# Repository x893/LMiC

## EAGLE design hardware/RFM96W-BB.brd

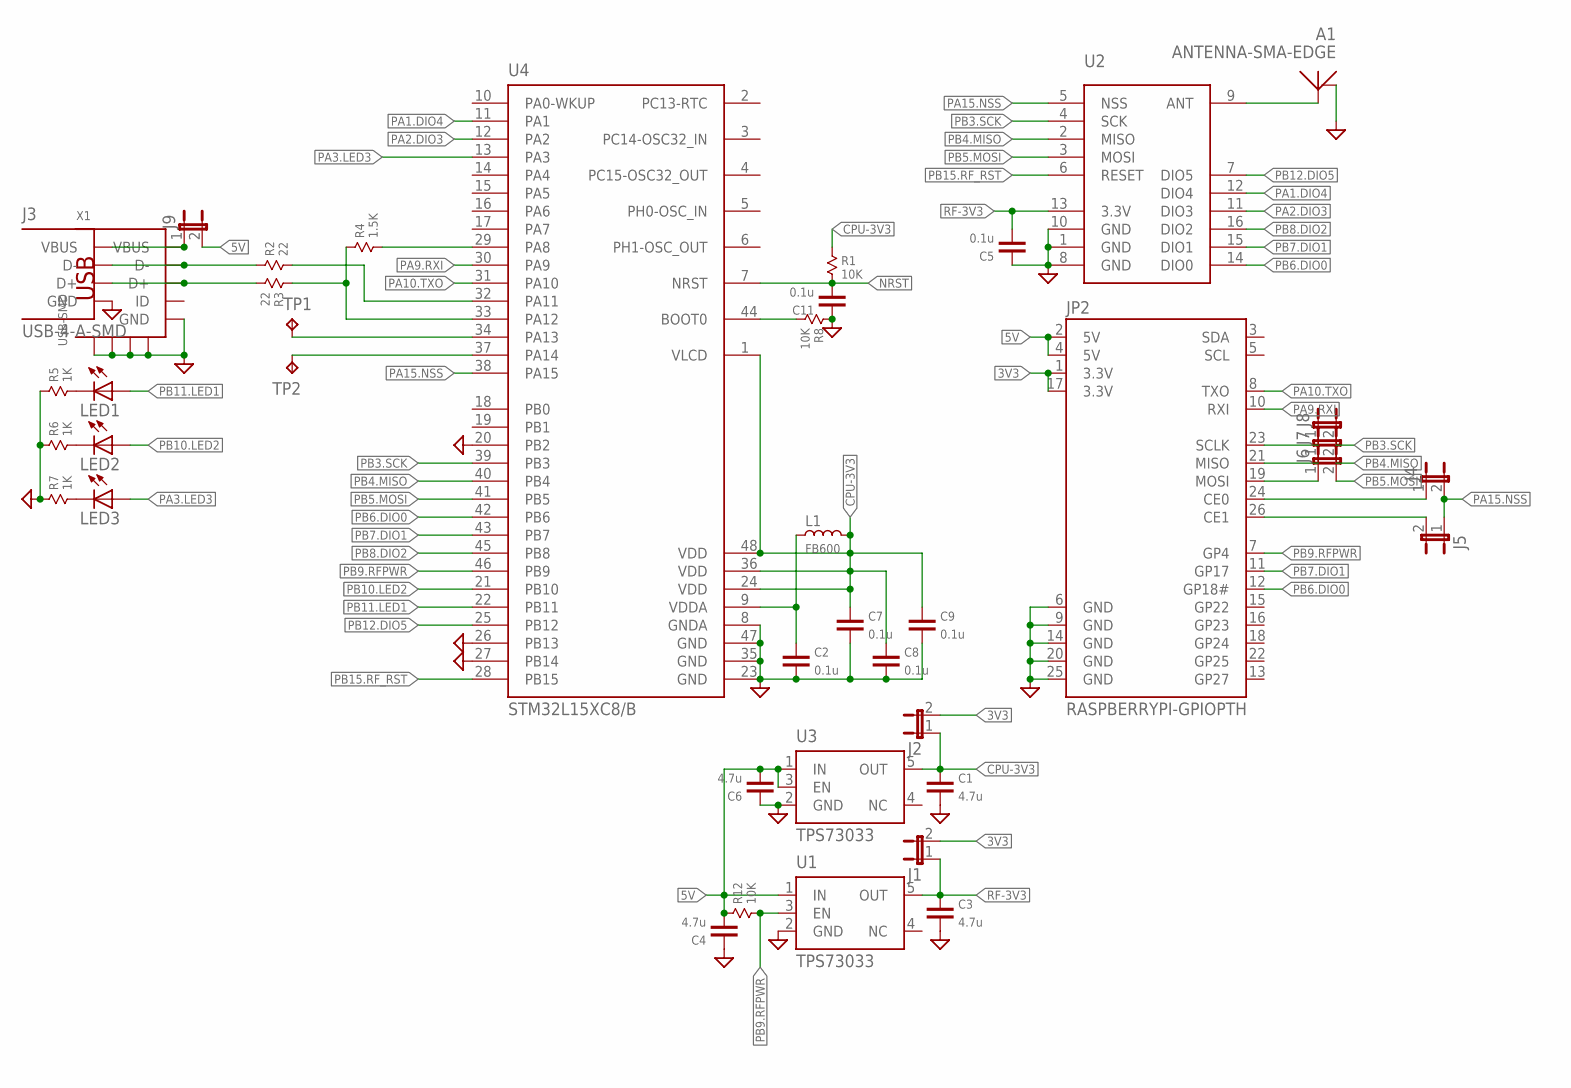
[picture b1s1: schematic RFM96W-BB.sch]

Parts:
A1: ANTENNA-SMA-EDGE; SMA-EDGE
C1, C3, C4, C6: 4.7u; 0603
C2, C5, C7, C8, C9, C11: 0.1u; 0603
J1, J2, J4, J5, J6, J7, J8, J9: JUMPER-2SMD-NO; SJ_2S-NO
J3: USB-4-A-SMD; USB-A-SMD
JP2: RASPBERRYPI-GPIOPTH; 2X13-SHROUDED
L1: FB600; 0603
LED1, LED2, LED3: LEDCHIPLED_0603; CHIPLED_0603
R1, R8, R12: 10K; 0603
R2, R3: 22; 0603
R4: 1.5K; 0603
R5, R6, R7: 1K; 0603
TP1, TP2: TPTP14R; TP14R
U1, U3: TPS73033; SOT23-5
U2: RFM9XW
U4: STM32L15XC8/B; LQFP48
X1: USB-SMD; USB-MINIB

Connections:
3V3: J1.2, J2.2, JP2.1 (3.3V), JP2.17 (3.3V)
5V: C4.1, C6.1, J9.2, JP2.2 (5V), JP2.4 (5V), R12.1, U1.1 (IN), U3.1 (IN), U3.3 (EN)
CPU-3V3: C1.2, C7.2, C8.2, C9.2, J2.1, L1.2, R1.1, U3.5 (OUT), U4.1 (VLCD), U4.24 (VDD), U4.36 (VDD), U4.48 (VDD)
GND: A1.GND@1 (GND), C1.1, C2.1, C3.1, C4.2, C5.2, C6.2, C7.1, C8.1, C9.1, C11.2, J3.GND, JP2.6 (GND), JP2.9 (GND), JP2.14 (GND), JP2.20 (GND), JP2.25 (GND), R5.1, R6.1, R7.1, R8.1, U1.2 (GND), U2.1 (GND), U2.8 (GND), U2.10 (GND), U3.2 (GND), U4.8 (GNDA), U4.20 (PB2), U4.23 (GND), U4.26 (PB13), U4.27 (PB14), U4.35 (GND), U4.47 (GND), X1.GND, X1.GND@1 (GND), X1.GND@2 (GND), X1.GND@3 (GND), X1.GND@4 (GND)
unnamed: C2.2, L1.1, U4.9 (VDDA)
unnamed: A1.ANT, U2.9 (ANT)
unnamed: J3.VUSB (VBUS), J9.1, X1.VBUS
unnamed: J3.D-, R2.1, X1.D-
unnamed: J3.D+, R3.2, X1.D+
unnamed: J8.1, JP2.23 (SCLK)
unnamed: J7.1, JP2.21 (MISO)
unnamed: J4.1, JP2.24 (CE0)
unnamed: J5.2, JP2.26 (CE1)
unnamed: R8.2, U4.44 (BOOT0)
unnamed: LED1.C, R5.2
unnamed: LED2.C, R6.2
unnamed: LED3.C, R7.2
NRST: C11.1, R1.2, U4.7 (NRST)
PA1.DIO4: U2.12 (DIO4), U4.11 (PA1)
PA2.DIO3: U2.11 (DIO3), U4.12 (PA2)
PA3.LED3: LED3.A, U4.13 (PA3)
PA8.D+H: R4.2, U4.29 (PA8)
PA9.RXI: JP2.10 (RXI), U4.30 (PA9)
PA10.TXO: JP2.8 (TXO), U4.31 (PA10)
PA11.D-: R2.2, U4.32 (PA11)
PA12.D+: R3.1, R4.1, U4.33 (PA12)
PA13: TP1.TP, U4.34 (PA13)
PA14: TP2.TP, U4.37 (PA14)
PA15.NSS: J4.2, J5.1, U2.5 (NSS), U4.38 (PA15)
PB3.SCK: J8.2, U2.4 (SCK), U4.39 (PB3)
PB4.MISO: J7.2, U2.2 (MISO), U4.40 (PB4)
PB5.MOSI: J6.2, U2.3 (MOSI), U4.41 (PB5)
PB6.DIO0: JP2.12 (GP18#), U2.14 (DIO0), U4.42 (PB6)
PB7.DIO1: JP2.11 (GP17), U2.15 (DIO1), U4.43 (PB7)
PB8.DIO2: U2.16 (DIO2), U4.45 (PB8)
PB9.RFPWR: JP2.7 (GP4), R12.2, U1.3 (EN), U4.46 (PB9)
PB10.LED2: LED2.A, U4.21 (PB10)
PB11.LED1: LED1.A, U4.22 (PB11)
PB12.DIO5: U2.7 (DIO5), U4.25 (PB12)
PB15.RF_RST: U2.6 (RESET), U4.28 (PB15)
R-MOSI: J6.1, JP2.19 (MOSI)
RF-3V3: C3.2, C5.1, J1.1, U1.5 (OUT), U2.13 (3.3V)

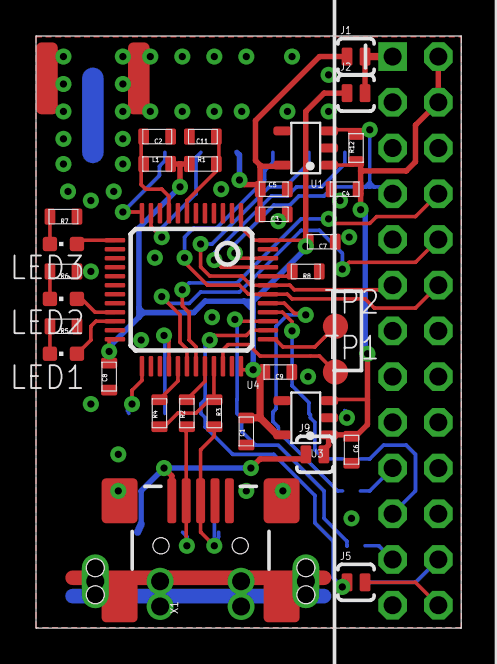
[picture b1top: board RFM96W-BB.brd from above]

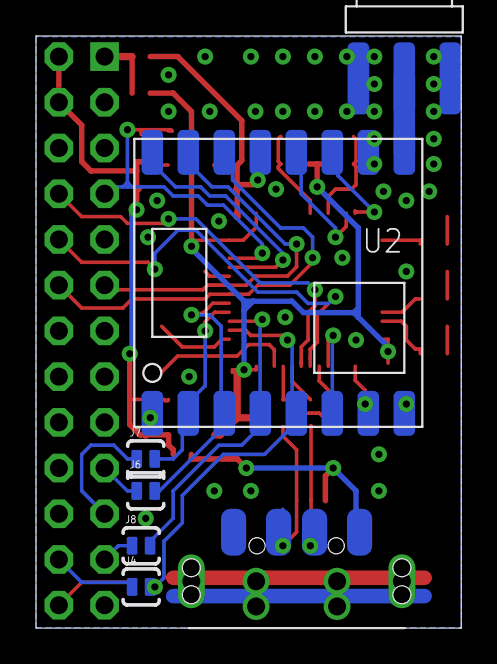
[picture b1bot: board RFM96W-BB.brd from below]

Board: 2 copper layers, 23.6 x 32.9 mm, 41 parts (7 on the bottom side), 42 nets.

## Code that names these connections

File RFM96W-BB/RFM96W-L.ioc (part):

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Mcu.Name=STM32L151C(6-8-B)Tx
Mcu.Package=LQFP48
Mcu.UserName=STM32L151CBTx
PA1.GPIOParameters=GPIO_PuPd,GPIO_Label,GPIO_Mode
PA1.GPIO_Label=DIO4
PA1.GPIO_Mode=GPIO_MODE_INPUT
PA1.GPIO_PuPd=GPIO_NOPULL
PA1.Signal=GPIO_Input
PA10.GPIOParameters=GPIO_Speed,GPIO_PuPd,GPIO_Mode
PA10.GPIO_Mode=GPIO_MODE_AF_PP
PA10.GPIO_PuPd=GPIO_PULLUP
PA10.GPIO_Speed=GPIO_SPEED_HIGH
PA10.Mode=Asynchronous
PA10.Signal=USART1_RX
PA11.Mode=Device
PA11.Signal=USB_DM
PA12.GPIOParameters=GPIO_Speed,GPIO_PuPd,GPIO_Mode
PA12.GPIO_Mode=GPIO_MODE_AF_PP
PA12.GPIO_PuPd=GPIO_NOPULL
PA12.GPIO_Speed=GPIO_Speed_40MHz
PA12.Mode=Device
PA12.Signal=USB_DP
PA13.GPIOParameters=GPIO_Label
PA13.GPIO_Label=SWD
PA13.Mode=Serial-Wire
PA13.Signal=SYS_JTMS-SWDIO
PA14.GPIOParameters=GPIO_Label
PA14.GPIO_Label=SWC
PA14.Mode=Serial-Wire
PA14.Signal=SYS_JTCK-SWCLK
PA15.GPIOParameters=GPIO_Speed,GPIO_PuPd,GPIO_Label,GPIO_ModeDefaultOutputPP
PA15.GPIO_Label=SPI1_NSS
PA15.GPIO_ModeDefaultOutputPP=GPIO_MODE_OUTPUT_PP
PA15.GPIO_PuPd=GPIO_NOPULL
PA15.GPIO_Speed=GPIO_SPEED_VERY_LOW
PA15.Signal=GPIO_Output
PA2.GPIOParameters=GPIO_PuPd,GPIO_Label,GPIO_Mode
PA2.GPIO_Label=DIO3
PA2.GPIO_Mode=GPIO_MODE_INPUT
PA2.GPIO_PuPd=GPIO_NOPULL
PA2.Signal=GPIO_Input
PA3.GPIOParameters=GPIO_Speed,GPIO_PuPd,GPIO_Label,GPIO_ModeDefaultOutputPP,GPIO_Mode
PA3.GPIO_Label=LED3
PA3.GPIO_Mode=GPIO_MODE_OUTPUT_PP
PA3.GPIO_ModeDefaultOutputPP=GPIO_MODE_OUTPUT_PP
PA3.GPIO_PuPd=GPIO_NOPULL
PA3.GPIO_Speed=GPIO_SPEED_LOW
PA3.Signal=GPIO_Output
PA8.GPIOParameters=GPIO_Speed,GPIO_PuPd,GPIO_Label,GPIO_ModeDefaultOutputPP,GPIO_Mode
PA8.GPIO_Label=USB_ON
PA8.GPIO_Mode=GPIO_MODE_OUTPUT_PP
PA8.GPIO_ModeDefaultOutputPP=GPIO_MODE_OUTPUT_PP
PA8.GPIO_PuPd=GPIO_NOPULL
PA8.GPIO_Speed=GPIO_SPEED_LOW
PA8.Signal=GPIO_Output
PA9.GPIOParameters=GPIO_Speed,GPIO_PuPd,GPIO_Mode
PA9.GPIO_Mode=GPIO_MODE_AF_PP
PA9.GPIO_PuPd=GPIO_PULLUP
PA9.GPIO_Speed=GPIO_SPEED_HIGH
PA9.Mode=Asynchronous
PA9.Signal=USART1_TX
PB10.GPIOParameters=GPIO_Speed,GPIO_PuPd,GPIO_Label,GPIO_ModeDefaultOutputPP,GPIO_Mode
PB10.GPIO_Label=LED2
PB10.GPIO_Mode=GPIO_MODE_OUTPUT_PP
PB10.GPIO_ModeDefaultOutputPP=GPIO_MODE_OUTPUT_PP
PB10.GPIO_PuPd=GPIO_NOPULL
PB10.GPIO_Speed=GPIO_SPEED_LOW
PB10.Signal=GPIO_Output
PB11.GPIOParameters=GPIO_Speed,GPIO_PuPd,GPIO_Label,GPIO_ModeDefaultOutputPP,GPIO_Mode
PB11.GPIO_Label=LED1
PB11.GPIO_Mode=GPIO_MODE_OUTPUT_PP
PB11.GPIO_ModeDefaultOutputPP=GPIO_MODE_OUTPUT_PP
PB11.GPIO_PuPd=GPIO_NOPULL
PB11.GPIO_Speed=GPIO_SPEED_LOW
PB11.Signal=GPIO_Output
PB12.GPIOParameters=GPIO_PuPd,GPIO_Label,GPIO_Mode
PB12.GPIO_Label=DIO5
PB12.GPIO_Mode=GPIO_MODE_INPUT
PB12.GPIO_PuPd=GPIO_NOPULL
PB12.Signal=GPIO_Input
PB15.GPIOParameters=GPIO_PuPd,GPIO_Label,GPIO_Mode
PB15.GPIO_Label=RFRST
PB15.GPIO_Mode=GPIO_MODE_INPUT
PB15.GPIO_PuPd=GPIO_PULLDOWN
PB15.Signal=GPIO_Input
PB3.GPIOParameters=GPIO_Speed,GPIO_PuPd,GPIO_Mode
PB3.GPIO_Mode=GPIO_MODE_AF_PP
PB3.GPIO_PuPd=GPIO_NOPULL
PB3.GPIO_Speed=GPIO_SPEED_HIGH
PB3.Mode=Full_Duplex_Master
PB3.Signal=SPI1_SCK
PB4.GPIOParameters=GPIO_Speed,GPIO_PuPd,GPIO_OType,GPIO_Mode
PB4.GPIO_Mode=GPIO_MODE_INPUT
PB4.GPIO_OType=N/A
PB4.GPIO_PuPd=GPIO_NOPULL
PB4.GPIO_Speed=N/A
PB4.Mode=Full_Duplex_Master
PB4.Signal=SPI1_MISO
PB5.GPIOParameters=GPIO_Speed,GPIO_PuPd,GPIO_Mode
PB5.GPIO_Mode=GPIO_MODE_AF_PP
PB5.GPIO_PuPd=GPIO_NOPULL
PB5.GPIO_Speed=GPIO_SPEED_HIGH
PB5.Mode=Full_Duplex_Master
PB5.Signal=SPI1_MOSI
PB6.GPIOParameters=GPIO_PuPd,GPIO_Label,GPIO_ModeDefaultEXTI
PB6.GPIO_Label=DIO0
PB6.GPIO_ModeDefaultEXTI=GPIO_MODE_IT_RISING
PB6.GPIO_PuPd=GPIO_PULLDOWN
PB6.Signal=GPXTI6
PB7.GPIOParameters=GPIO_PuPd,GPIO_Label,GPIO_Mode
PB7.GPIO_Label=DIO1
PB7.GPIO_Mode=GPIO_MODE_INPUT
PB7.GPIO_PuPd=GPIO_NOPULL
PB7.Signal=GPIO_Input
PB8.GPIOParameters=GPIO_PuPd,GPIO_Label,GPIO_Mode
PB8.GPIO_Label=DIO2
PB8.GPIO_Mode=GPIO_MODE_INPUT
PB8.GPIO_PuPd=GPIO_NOPULL
PB8.Signal=GPIO_Input
PB9.GPIOParameters=GPIO_Speed,GPIO_PuPd,GPIO_Label,GPIO_ModeDefaultOutputPP,GPIO_Mode
PB9.GPIO_Label=RFPWR
PB9.GPIO_Mode=GPIO_MODE_OUTPUT_PP
PB9.GPIO_ModeDefaultOutputPP=GPIO_MODE_OUTPUT_PP
PB9.GPIO_PuPd=GPIO_NOPULL
PB9.GPIO_Speed=GPIO_SPEED_LOW
PB9.Signal=GPIO_Output
RCC.HSE_VALUE=24000000
RCC.SYSCLKFreq_VALUE=32000000
RCC.SYSCLKSource=RCC_SYSCLKSOURCE_PLLCLK

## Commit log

2015-02-22 Initial commit for RFM98W and custom board STM32L151CB
2015-02-24 Start add RFM98W support
2015-02-25 Fix LSE TIM9 Add RadioHead support
2015-09-07 Working commit

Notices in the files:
parts and their libraries:
SparkFun-Boards: Licensing: CC v3.0 Share-Alike You are welcome to use this library for commercial purposes.
